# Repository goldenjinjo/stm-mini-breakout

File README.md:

# stm-mini-breakout
Breakout board for STM32H723ZGT6 MCU. Powered and programmed via USB C (FS). WIP.

Demonstration board for high-powered STM32s. 

## Schematics

# MCU

# Communication and Power

# Filtering, HSE Clock and Mounting Holes

## PCB Layout

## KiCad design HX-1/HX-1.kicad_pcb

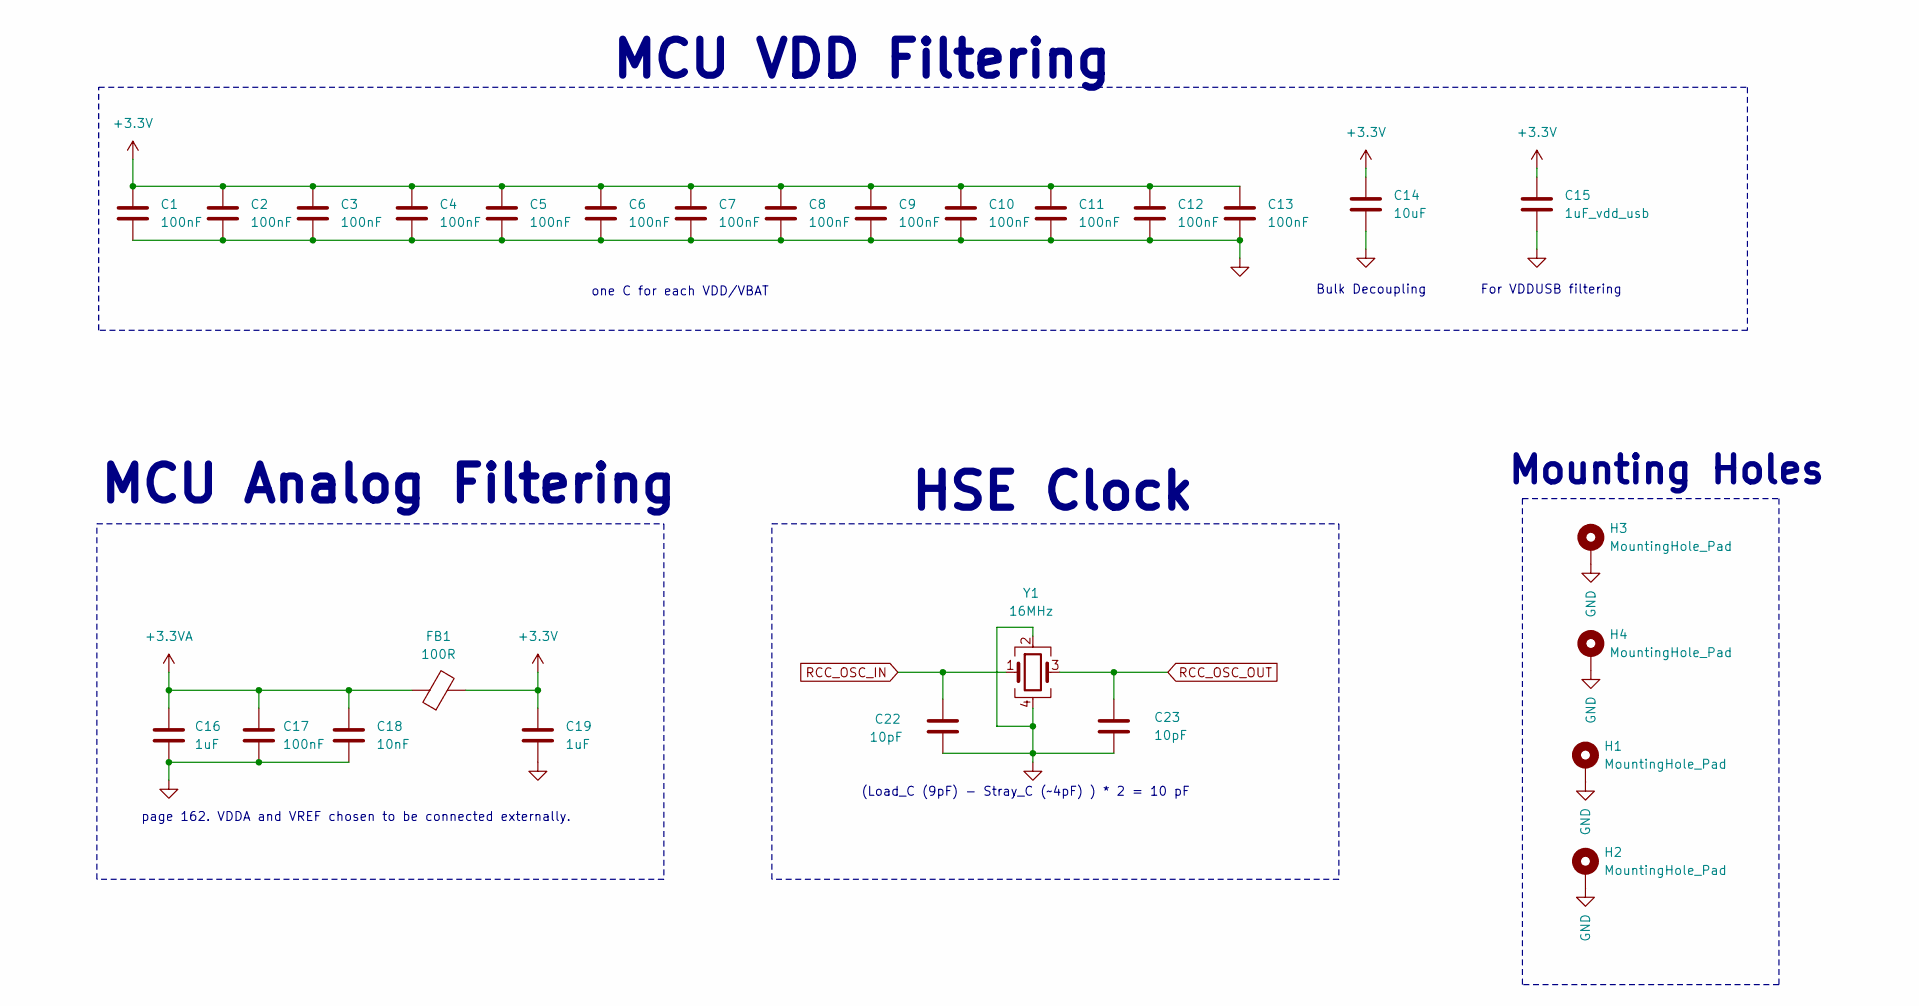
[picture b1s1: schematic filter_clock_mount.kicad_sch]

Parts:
C1, C2, C3, C4, C5, C6, C7, C8, C9, C10, C11, C12, C13, C17: 100nF; C_0402_1005Metric; LCSC PN C1525
C14: 10uF; C_0603_1608Metric; LCSC PN C19702
C15: 1uF_vdd_usb; C_0603_1608Metric; LCSC PN C15849
C16, C19: 1uF; C_0402_1005Metric; LCSC PN C52923
C18: 10nF; C_0603_1608Metric; LCSC PN C173276
C22, C23: 10pF; C_0603_1608Metric; LCSC PN C1634
FB1: 100R; R_0805_2012Metric; LCSC PN C1015
H1, H2, H3, H4: MountingHole_Pad; MountingHole_3.2mm_M3_Pad
Y1: 16MHz; Crystal_SMD_3225-4Pin_3.2x2.5mm; LCSC PN C13738

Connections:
+3.3V: C1.1, C2.1, C3.1, C4.1, C5.1, C6.1, C7.1, C8.1, C9.1, C10.1, C11.1, C12.1, C13.1, C14.1, C15.1, C19.1, FB1.2; also elsewhere on the board
+3.3VA: C16.1, C17.1, C18.1, FB1.1; also elsewhere on the board
GND: C1.2, C2.2, C3.2, C4.2, C5.2, C6.2, C7.2, C8.2, C9.2, C10.2, C11.2, C12.2, C13.2, C14.2, C15.2, C16.2, C17.2, C18.2, C19.2, C22.1, C23.2, H1.1, H2.1, H3.1, H4.1, Y1.2, Y1.4; also elsewhere on the board
RCC_OSC_IN: C22.2, Y1.1; also elsewhere on the board
RCC_OSC_OUT: C23.1, Y1.3; also elsewhere on the board

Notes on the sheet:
Bulk Decoupling
MCU Analog Filtering
page 162. VDDA and VREF chosen to be connected externally.
(Load_C (9pF) - Stray_C (~4pF) ) * 2 = 10 pF
one C for each VDD/VBAT
For VDDUSB filtering
HSE Clock
MCU VDD Filtering
Mounting Holes

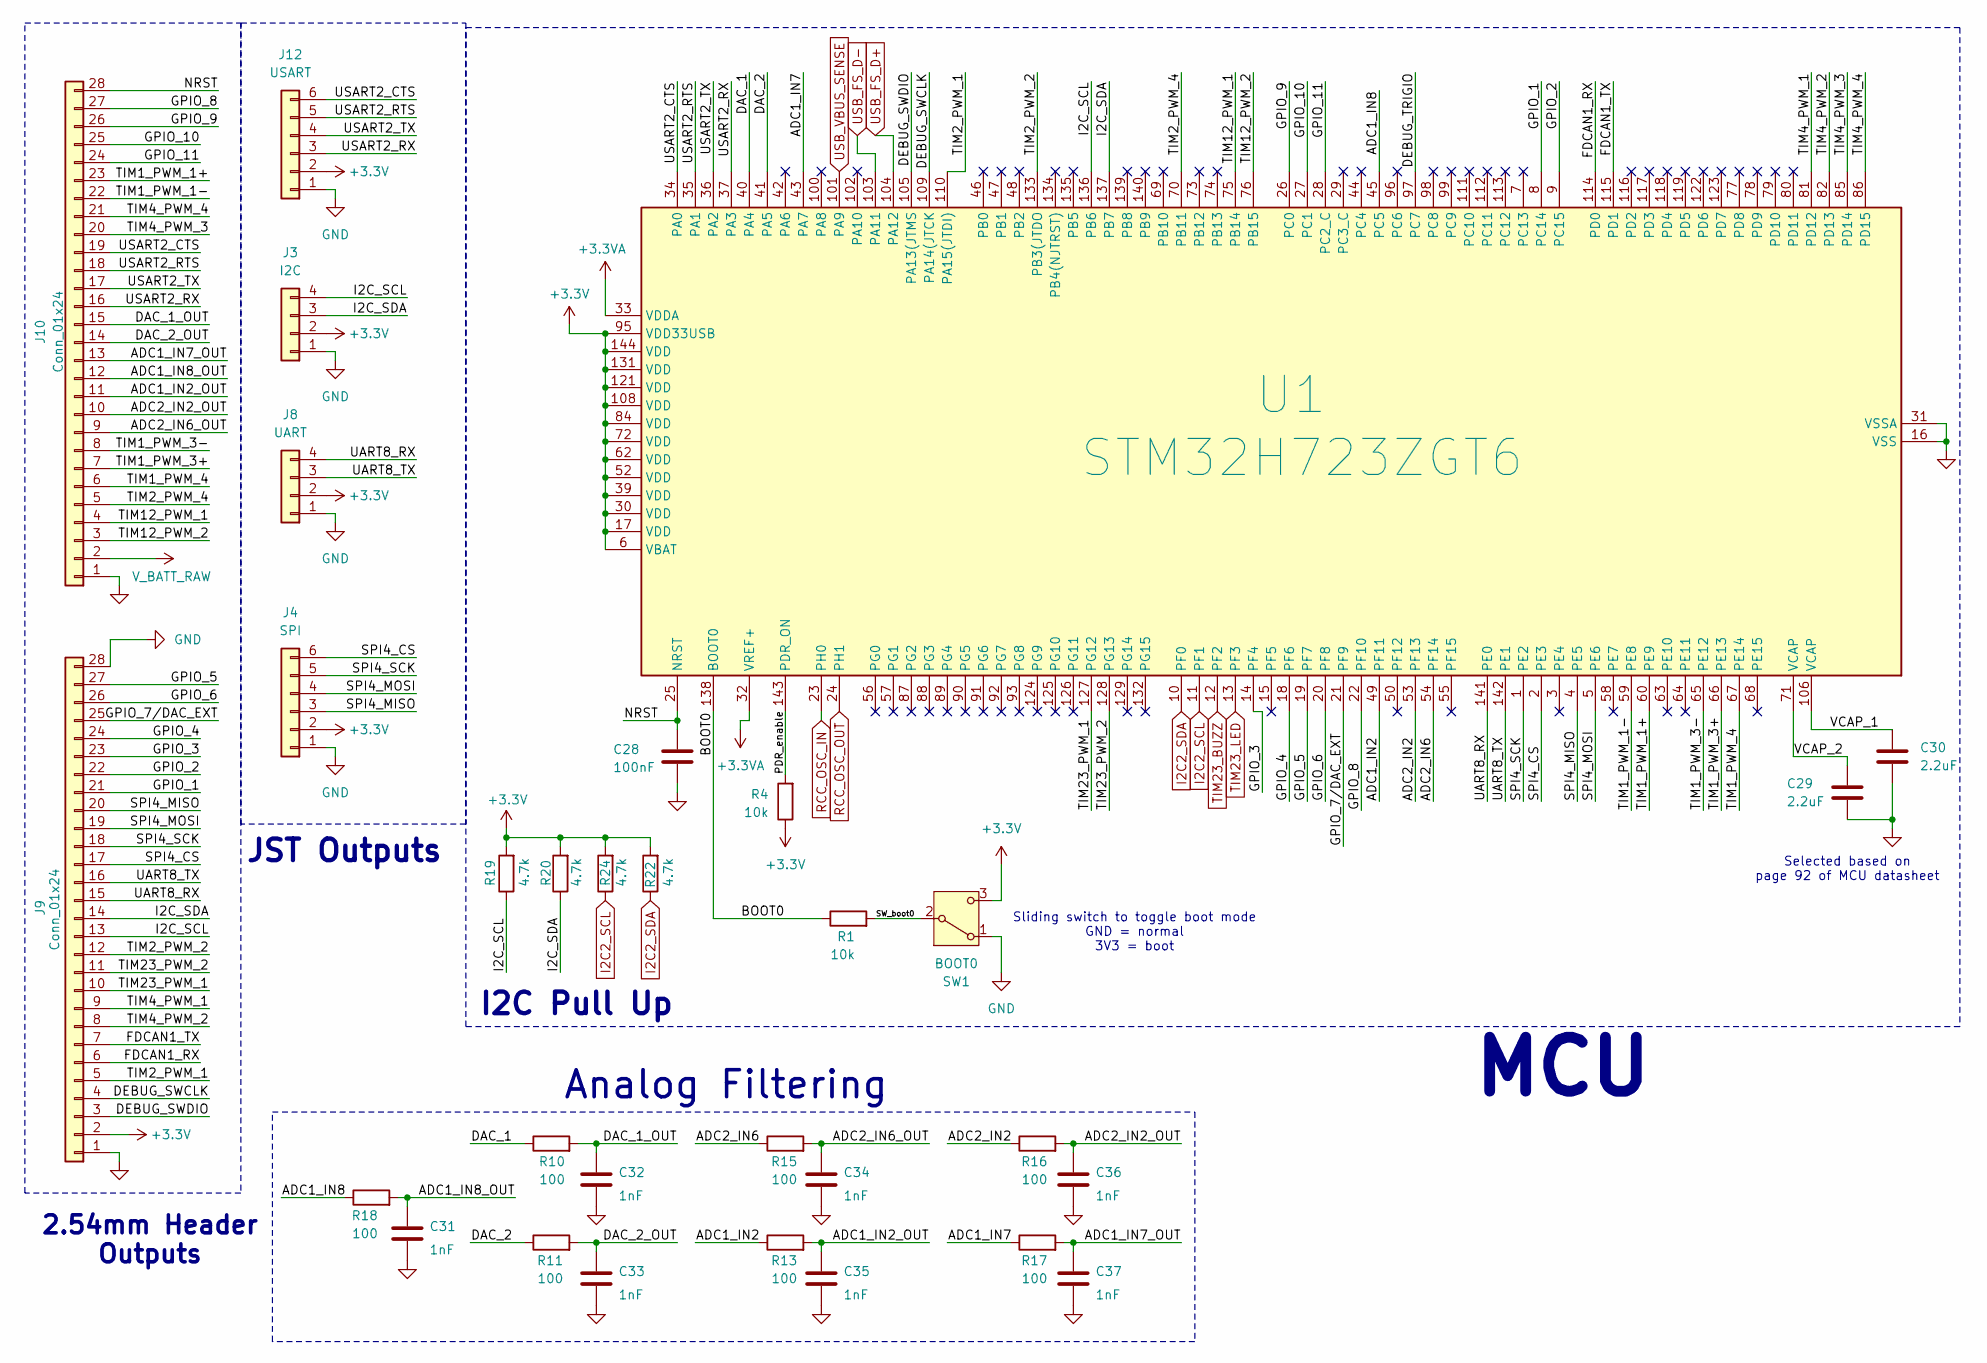
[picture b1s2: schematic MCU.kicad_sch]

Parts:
C28: 100nF; C_0402_1005Metric; LCSC PN C1525
C29, C30: 2.2uF; C_0603_1608Metric; LCSC PN C23630
C31, C32, C33, C34, C35, C36, C37: 1nF; C_0603_1608Metric; LCSC PN C1588
J3: I2C; JST_PH_B4B-PH-K_1x04_P2.00mm_Vertical; LCSC PN C131334
J4: SPI; JST_PH_B6B-PH-K_1x06_P2.00mm_Vertical; LCSC PN C131342
J8: UART; JST_PH_B4B-PH-K_1x04_P2.00mm_Vertical; LCSC PN C131334
J9, J10: Conn_01x24; PinHeader_1x28_P2.54mm_Vertical
J12: USART; JST_PH_B6B-PH-K_1x06_P2.00mm_Vertical; LCSC PN C131342
R1, R4: 10k; R_0402_1005Metric; LCSC PN C25744
R10, R11, R13, R15, R16, R17, R18: 100; R_0402_1005Metric; LCSC PN C25076
R19, R20, R22, R24: 4.7k; R_0402_1005Metric; LCSC PN C25900
SW1: BOOT0; SW-TH_G-SWITCH_SS-12F20-G070; LCSC PN C2848914
U1: STM32H723ZGT6; LQFP-144_20x20mm_P0.5mm; LCSC PN C730146

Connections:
+3.3V: J3.2, J4.2, J8.2, J9.2, J12.2, R4.1, R19.2, R20.2, R22.2, R24.2, SW1.3 (C), U1.6 (VBAT), U1.17 (VDD), U1.30 (VDD), U1.39 (VDD), U1.52 (VDD), U1.62 (VDD), U1.72 (VDD), U1.84 (VDD), U1.95 (VDD33USB), U1.108 (VDD), U1.121 (VDD), U1.131 (VDD), U1.144 (VDD); also elsewhere on the board
+3.3VA: U1.32 (VREF+), U1.33 (VDDA); also elsewhere on the board
/MCU/ADC1_IN2: R13.1, U1.49 (PF11)
/MCU/ADC1_IN2_OUT: C35.1, J10.11, R13.2
/MCU/ADC1_IN7: R17.1, U1.43 (PA7)
/MCU/ADC1_IN7_OUT: C37.1, J10.13, R17.2
/MCU/ADC1_IN8: R18.1, U1.45 (PC5)
/MCU/ADC1_IN8_OUT: C31.1, J10.12, R18.2
/MCU/ADC2_IN2: R16.1, U1.53 (PF13)
/MCU/ADC2_IN2_OUT: C36.1, J10.10, R16.2
/MCU/ADC2_IN6: R15.1, U1.54 (PF14)
/MCU/ADC2_IN6_OUT: C34.1, J10.9, R15.2
/MCU/BOOT0: R1.1, U1.138 (BOOT0)
/MCU/DAC_1: R10.1, U1.40 (PA4)
/MCU/DAC_1_OUT: C32.1, J10.15, R10.2
/MCU/DAC_2: R11.1, U1.41 (PA5)
/MCU/DAC_2_OUT: C33.1, J10.14, R11.2
/MCU/DEBUG_SWCLK: J9.4, U1.109 (PA14(JTCK)
/MCU/DEBUG_SWDIO: J9.3, U1.105 (PA13(JTMS)
/MCU/DEBUG_TRIGIO: U1.97 (PC7)
/MCU/FDCAN1_RX: J9.6, U1.114 (PD0)
/MCU/FDCAN1_TX: J9.7, U1.115 (PD1)
/MCU/GPIO_1: J9.21, U1.8 (PC14)
/MCU/GPIO_2: J9.22, U1.9 (PC15)
/MCU/GPIO_3: J9.23, U1.14 (PF4)
/MCU/GPIO_4: J9.24, U1.18 (PF6)
/MCU/GPIO_5: J9.27, U1.19 (PF7)
/MCU/GPIO_6: J9.26, U1.20 (PF8)
/MCU/GPIO_7/DAC_EXT: J9.25, U1.21 (PF9)
/MCU/GPIO_8: J10.27, U1.22 (PF10)
/MCU/GPIO_9: J10.26, U1.26 (PC0)
/MCU/GPIO_10: J10.25, U1.27 (PC1)
/MCU/GPIO_11: J10.24, U1.28 (PC2_C)
/MCU/I2C_SCL: J3.4, J9.13, R19.1, U1.136 (PB6)
/MCU/I2C_SDA: J3.3, J9.14, R20.1, U1.137 (PB7)
/MCU/NRST: C28.1, J10.28, U1.25 (NRST)
/MCU/PDR_enable: R4.2, U1.143 (PDR_ON)
/MCU/SPI4_CS: J4.6, J9.17, U1.2 (PE3)
/MCU/SPI4_MISO: J4.3, J9.20, U1.4 (PE5)
/MCU/SPI4_MOSI: J4.4, J9.19, U1.5 (PE6)
/MCU/SPI4_SCK: J4.5, J9.18, U1.1 (PE2)
/MCU/SW_boot0: R1.2, SW1.2 (B)
/MCU/TIM1_PWM_1+: J10.23, U1.60 (PE9)
/MCU/TIM1_PWM_1-: J10.22, U1.59 (PE8)
/MCU/TIM1_PWM_3+: J10.7, U1.66 (PE13)
/MCU/TIM1_PWM_3-: J10.8, U1.65 (PE12)
/MCU/TIM1_PWM_4: J10.6, U1.67 (PE14)
/MCU/TIM2_PWM_1: J9.5, U1.110 (PA15(JTDI))
/MCU/TIM2_PWM_2: J9.12, U1.133 (PB3(JTDO)
/MCU/TIM2_PWM_4: J10.5, U1.70 (PB11)
/MCU/TIM4_PWM_1: J9.9, U1.81 (PD12)
/MCU/TIM4_PWM_2: J9.8, U1.82 (PD13)
/MCU/TIM4_PWM_3: J10.20, U1.85 (PD14)
/MCU/TIM4_PWM_4: J10.21, U1.86 (PD15)
/MCU/TIM12_PWM_1: J10.4, U1.75 (PB14)
/MCU/TIM12_PWM_2: J10.3, U1.76 (PB15)
/MCU/TIM23_PWM_1: J9.10, U1.127 (PG12)
/MCU/TIM23_PWM_2: J9.11, U1.128 (PG13)
/MCU/UART8_RX: J8.4, J9.15, U1.141 (PE0)
/MCU/UART8_TX: J8.3, J9.16, U1.142 (PE1)
/MCU/USART2_CTS: J10.19, J12.6, U1.34 (PA0)
/MCU/USART2_RTS: J10.18, J12.5, U1.35 (PA1)
/MCU/USART2_RX: J10.16, J12.3, U1.37 (PA3)
/MCU/USART2_TX: J10.17, J12.4, U1.36 (PA2)
/MCU/VCAP_1: C30.1, U1.106 (VCAP)
/MCU/VCAP_2: C29.1, U1.71 (VCAP)
GND: C28.2, C29.2, C30.2, C31.2, C32.2, C33.2, C34.2, C35.2, C36.2, C37.2, J3.1, J4.1, J8.1, J9.1, J9.28, J10.1, J12.1, SW1.1 (A), U1.16 (VSS), U1.31 (VSSA), U1.38 (VSS), U1.51 (VSS), U1.61 (VSS), U1.83 (VSS), U1.94 (VSS), U1.107 (VSS), U1.120 (VSS), U1.130 (VSS); also elsewhere on the board
I2C2_SCL: R24.1, U1.11 (PF1); also elsewhere on the board
I2C2_SDA: R22.1, U1.10 (PF0); also elsewhere on the board
RCC_OSC_IN: U1.23 (PH0); also elsewhere on the board
RCC_OSC_OUT: U1.24 (PH1); also elsewhere on the board
TIM23_BUZZ: U1.12 (PF2); also elsewhere on the board
TIM23_LED: U1.13 (PF3); also elsewhere on the board
USB_FS_D+: U1.104 (PA12); also elsewhere on the board
USB_FS_D-: U1.103 (PA11); also elsewhere on the board
USB_VBUS_SENSE: U1.101 (PA9); also elsewhere on the board
V_BATT_RAW: J10.2; also elsewhere on the board

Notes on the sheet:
JST Outputs
2.54mm Header Outputs
MCU
Sliding switch to toggle boot mode GND = normal 3V3 = boot
I2C Pull Up
Analog Filtering
Selected based on page 92 of MCU datasheet

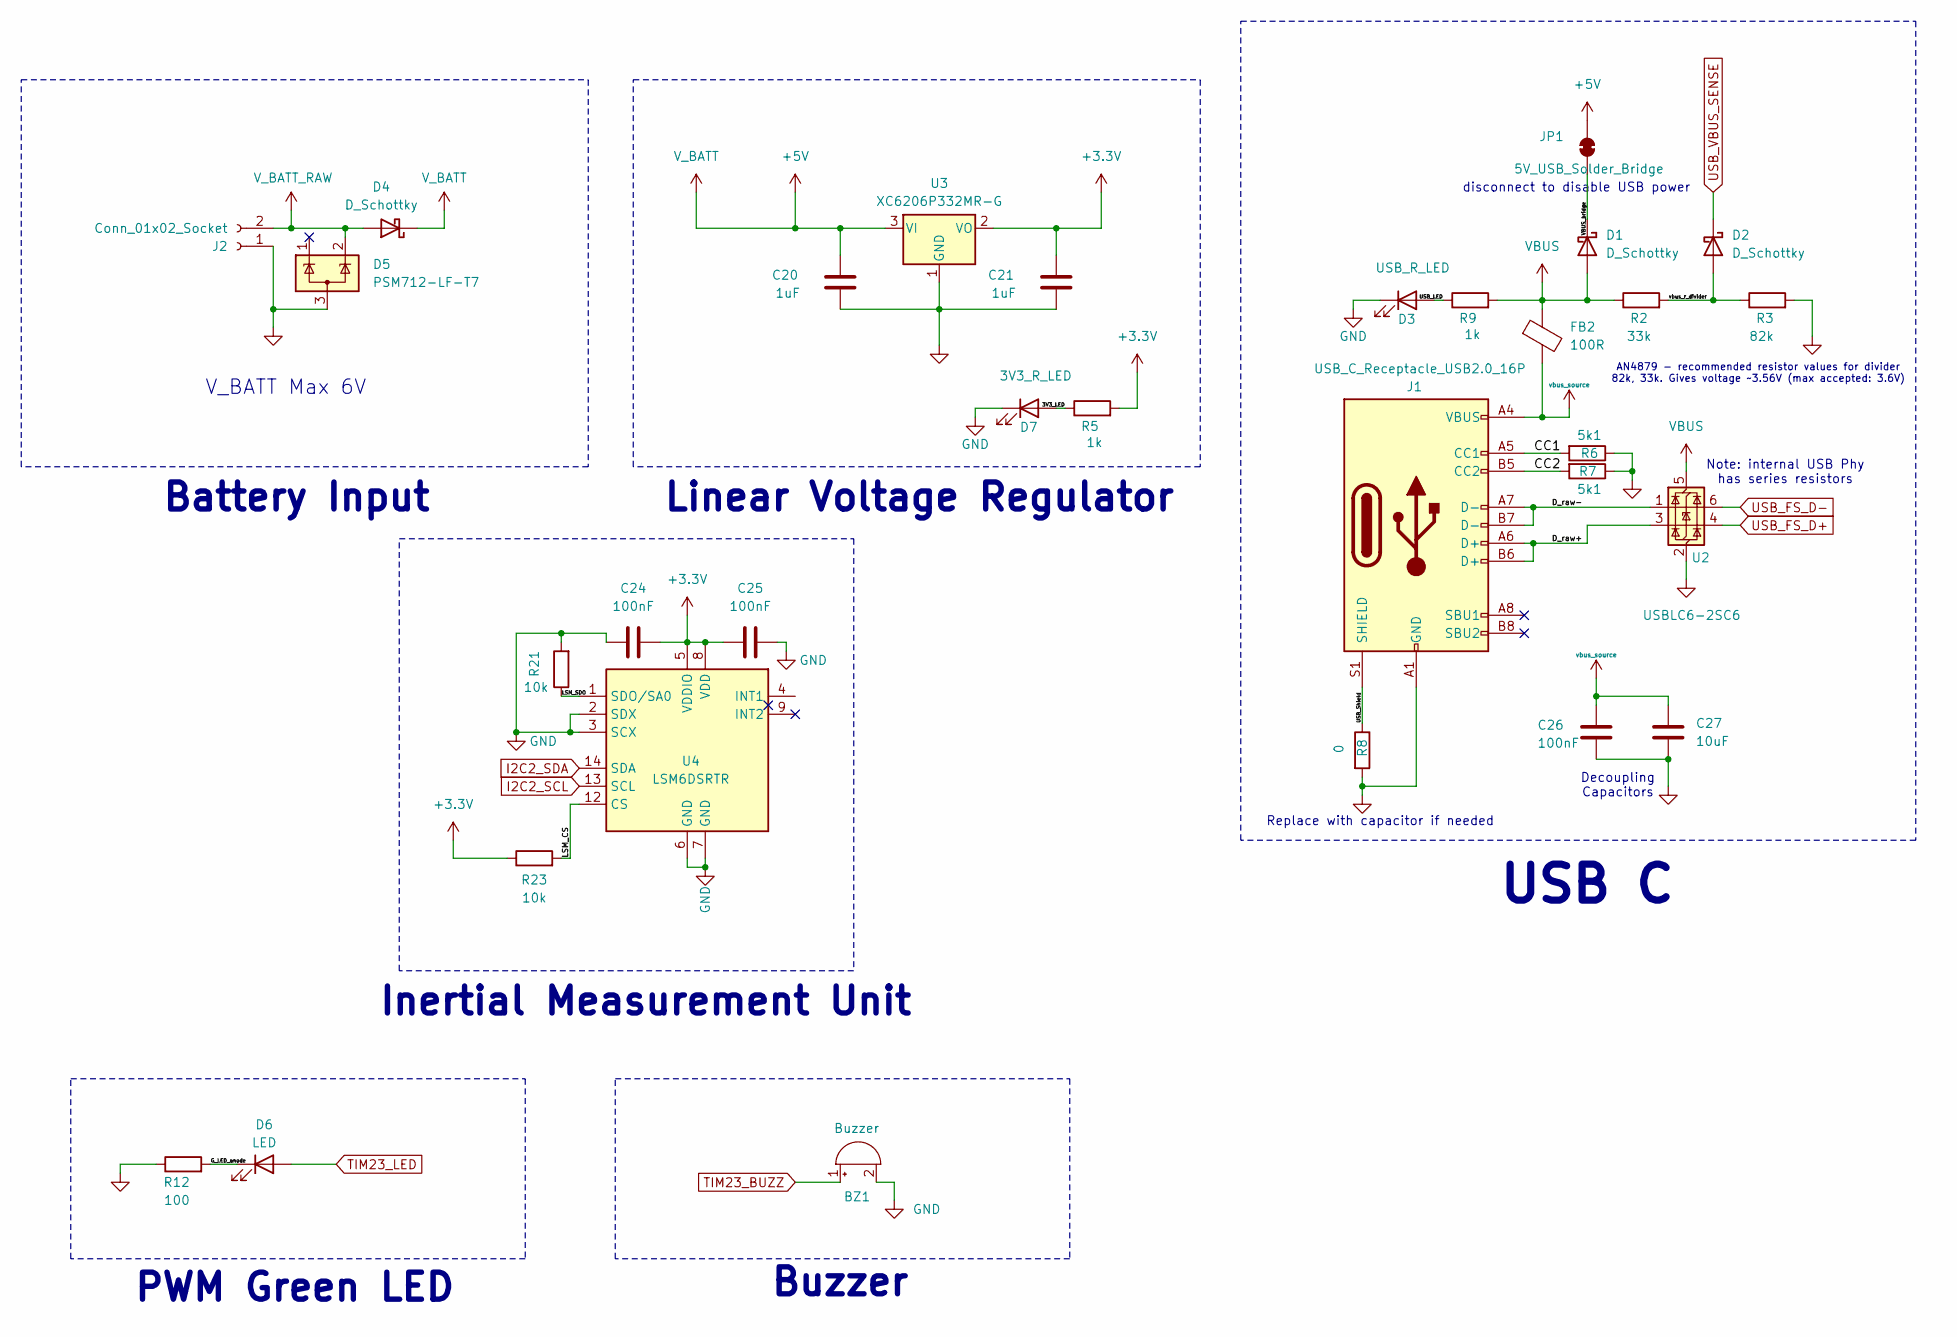
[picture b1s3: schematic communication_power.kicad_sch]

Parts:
BZ1: Buzzer; YUEXIN YX-SMD5020; LCSC PN C781883
C20, C21: 1uF; C_0402_1005Metric; LCSC PN C52923
C24, C25, C26: 100nF; C_0402_1005Metric; LCSC PN C1525
C27: 10uF; C_0603_1608Metric; LCSC PN C19702
D1, D2, D4: D_Schottky; D_SOD-323; LCSC PN C191023
D3: USB_R_LED; LED_0603_1608Metric; LCSC PN C2286
D5: PSM712-LF-T7; SOT-23-3; LCSC PN C32677
D6: LED; LED_0805_2012Metric; LCSC PN C2297
D7: 3V3_R_LED; LED_0603_1608Metric; LCSC PN C2286
FB2: 100R; R_0805_2012Metric; LCSC PN C1015
J1: USB_C_Receptacle_USB2.0_16P; USB_C_Receptacle_G-Switch_GT-USB-7010ASV; LCSC PN C2988369
J2: Conn_01x02_Socket; JST_PH_B2B-PH-K_1x02_P2.00mm_Vertical; LCSC PN C131337
JP1: 5V_USB_Solder_Bridge; SolderJumper-2_P1.3mm_Bridged_RoundedPad1.0x1.5mm
R2: 33k; R_0603_1608Metric; LCSC PN C4216
R3: 82k; R_0603_1608Metric; LCSC PN C23254
R5, R9: 1k; R_0603_1608Metric; LCSC PN C21190
R6, R7: 5k1; R_0603_1608Metric; LCSC PN C23186
R8: 0; R_0603_1608Metric; LCSC PN C21189
R12: 100; R_0402_1005Metric; LCSC PN C25076
R21, R23: 10k; R_0402_1005Metric; LCSC PN C25744
U2: USBLC6-2SC6; SOT-23-6; LCSC PN C7519
U3: XC6206P332MR-G; SOT-23-3; LCSC PN C5446
U4: LSM6DSRTR; LGA-14_3x2.5mm_P0.5mm_LayoutBorder3x4y; LCSC PN C784817

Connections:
+3.3V: C21.2, C24.2, C25.1, R5.2, R23.1, U3.2 (VO), U4.5 (VDDIO), U4.8 (VDD); also elsewhere on the board
+5V: C20.2, D4.1 (K), JP1.2 (B), U3.3 (VI)
/Communication and Power/3V3_LED: D7.2 (A), R5.1
/Communication and Power/CC1: J1.A5 (CC1), R6.2
/Communication and Power/CC2: J1.B5 (CC2), R7.2
/Communication and Power/D_raw+: J1.A6 (D+), J1.B6 (D+), U2.3 (I/O2)
/Communication and Power/D_raw-: J1.A7 (D-), J1.B7 (D-), U2.1 (I/O1)
/Communication and Power/G_LED_anode: D6.1 (K), R12.2
/Communication and Power/LSM_CS: R23.2, U4.12 (CS)
/Communication and Power/LSM_SDO: R21.1, U4.1 (SDO/SA0)
/Communication and Power/USB_LED: D3.2 (A), R9.1
/Communication and Power/USB_Shield: J1.S1 (SHIELD), R8.1
/Communication and Power/VBUS_bridge: D1.1 (K), JP1.1 (A)
/Communication and Power/vbus_r_divider: D2.2 (A), R2.2, R3.1
GND: BZ1.2 (+), C20.1, C21.1, C24.1, C25.2, C26.2, C27.2, D3.1 (K), D5.3 (A), D7.1 (K), J1.A1 (GND), J1.A12 (GND), J1.B1 (GND), J1.B12 (GND), J2.1, R3.2, R6.1, R7.1, R8.2, R12.1, R21.2, U2.2 (GND), U3.1 (GND), U4.2 (SDX), U4.3 (SCX), U4.6 (GND), U4.7 (GND); also elsewhere on the board
I2C2_SCL: U4.13 (SCL); also elsewhere on the board
I2C2_SDA: U4.14 (SDA); also elsewhere on the board
TIM23_BUZZ: BZ1.1 (-); also elsewhere on the board
TIM23_LED: D6.2 (A); also elsewhere on the board
USB_FS_D+: U2.4 (I/O2); also elsewhere on the board
USB_FS_D-: U2.6 (I/O1); also elsewhere on the board
USB_VBUS_SENSE: D2.1 (K); also elsewhere on the board
VBUS: D1.2 (A), FB2.1, R2.1, R9.2, U2.5 (VBUS)
V_BATT_RAW: D4.2 (A), D5.2 (K), J2.2; also elsewhere on the board
vbus_source: C26.1, C27.1, FB2.2, J1.A4 (VBUS), J1.A9 (VBUS), J1.B4 (VBUS), J1.B9 (VBUS)

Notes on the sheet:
PWM Green LED
Battery Input
V_BATT Max 6V
Linear Voltage Regulator
Replace with capacitor if needed
AN4879 - recommended resistor values for divider 82k, 33k. Gives voltage ~3.56V (max accepted: 3.6V)
Decoupling Capacitors
Buzzer
disconnect to disable USB power
Inertial Measurement Unit
Note: internal USB Phy has series resistors
USB C

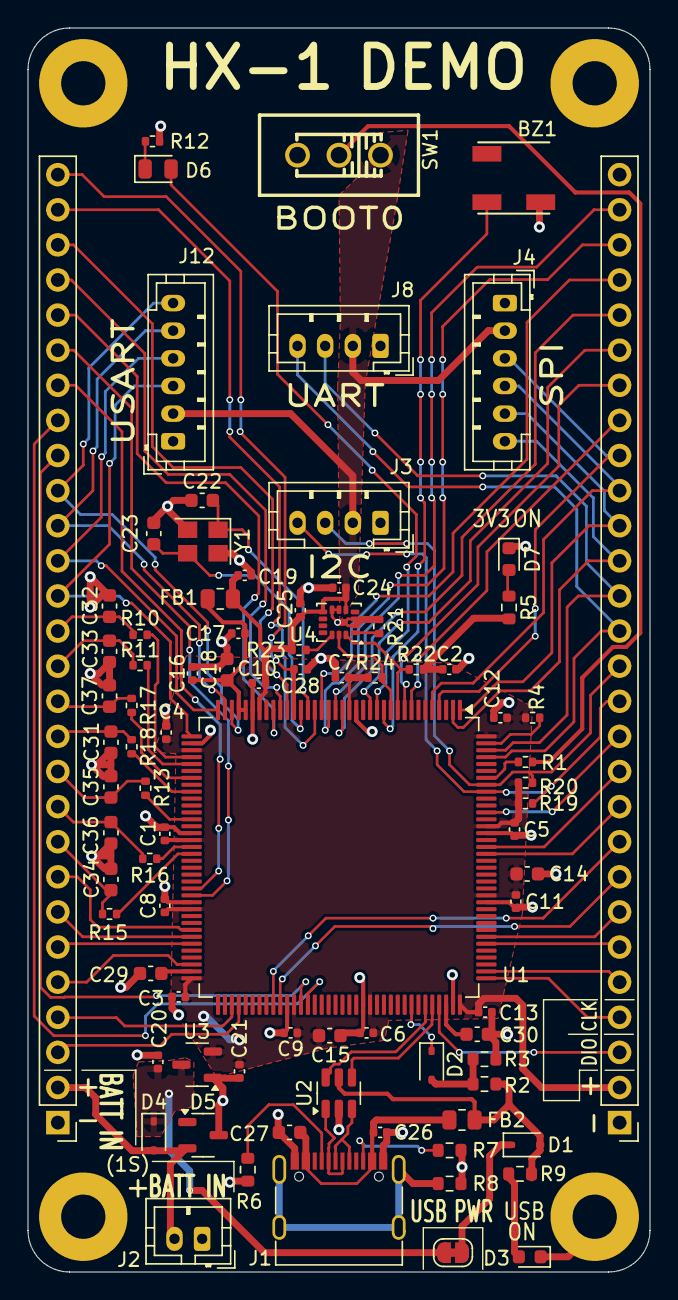
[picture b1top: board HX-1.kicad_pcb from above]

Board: 2 copper layers, 45.0 x 90.0 mm, 89 parts (0 on the bottom side), 91 nets.

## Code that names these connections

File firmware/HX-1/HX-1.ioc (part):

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Mcu.Name=STM32H723ZGTx
Mcu.Package=LQFP144
Mcu.UserName=STM32H723ZGTx
PA0.Mode=CTS_RTS
PA0.Signal=USART2_CTS
PA1.Mode=CTS_RTS
PA1.Signal=USART2_RTS
PA10.Signal=GPIO_Analog
PA11.Mode=Device_Only_FS
PA11.Signal=USB_OTG_HS_DM
PA12.Mode=Device_Only_FS
PA12.Signal=USB_OTG_HS_DP
PA13(JTMS/SWDIO).Mode=Serial_Wire
PA13(JTMS/SWDIO).Signal=DEBUG_JTMS-SWDIO
PA14(JTCK/SWCLK).Mode=Serial_Wire
PA14(JTCK/SWCLK).Signal=DEBUG_JTCK-SWCLK
PA15(JTDI).Signal=S_TIM2_CH1_ETR
PA2.Mode=Asynchronous
PA2.Signal=USART2_TX
PA3.Mode=Asynchronous
PA3.Signal=USART2_RX
PA4.Signal=COMP_DAC11_group
PA5.Signal=COMP_DAC12_group
PA6.Signal=GPIO_Analog
PA7.Signal=ADCx_INP7
PA8.Signal=GPIO_Analog
PA9.Mode=Activate_VBUS_FS
PA9.Signal=USB_OTG_HS_VBUS
PB0.Signal=GPIO_Analog
PB1.Signal=GPIO_Analog
PB10.Signal=GPIO_Analog
PB11.Signal=S_TIM2_CH4
PB13.Signal=GPIO_Analog
PB14.Signal=S_TIM12_CH1
PB15.Signal=S_TIM12_CH2
PB2.Signal=GPIO_Analog
PB3(JTDO/TRACESWO).Signal=S_TIM2_CH2
PB4(NJTRST).Signal=GPIO_Analog
PB5.Signal=GPIO_Analog
PB6.Mode=I2C
PB6.Signal=I2C1_SCL
PB7.Mode=I2C
PB7.Signal=I2C1_SDA
PB8.Signal=GPIO_Analog
PB9.Signal=GPIO_Analog
PC0.GPIOParameters=GPIO_Label
PC0.GPIO_Label=GPIO_9
PC0.Signal=GPIO_Output
PC1.GPIOParameters=GPIO_Label
PC1.GPIO_Label=GPIO_10
PC1.Signal=GPIO_Output
PC10.Signal=GPIO_Analog
PC11.Signal=GPIO_Analog
PC12.Signal=GPIO_Analog
PC13.Signal=GPIO_Analog
PC14-OSC32_IN.GPIOParameters=GPIO_Label
PC14-OSC32_IN.GPIO_Label=GPIO_1
PC14-OSC32_IN.Signal=GPIO_Output
PC15-OSC32_OUT.GPIOParameters=GPIO_Label
PC15-OSC32_OUT.GPIO_Label=GPIO_2
PC15-OSC32_OUT.Signal=GPIO_Output
PC2_C.GPIOParameters=GPIO_Label
PC2_C.GPIO_Label=GPIO_11
PC2_C.Signal=GPIO_Output
PC3_C.Signal=GPIO_Analog
PC4.Signal=GPIO_Analog
PC5.Signal=ADCx_INP8
PC6.Signal=GPIO_Analog
PC7.Mode=External_Trigger_bidirectional
PC7.Signal=DEBUG_TRGIO
PC8.Signal=GPIO_Analog
PC9.Signal=GPIO_Analog
PD0.Mode=FDCAN_Activate
PD0.Signal=FDCAN1_RX
PD1.Mode=FDCAN_Activate
PD1.Signal=FDCAN1_TX
PD10.Signal=GPIO_Analog
PD11.Signal=GPIO_Analog
PD12.Signal=S_TIM4_CH1
PD13.Signal=S_TIM4_CH2
PD14.Signal=S_TIM4_CH3
PD15.Signal=S_TIM4_CH4
PD2.Signal=GPIO_Analog
PD3.Signal=GPIO_Analog
PD4.Signal=GPIO_Analog
PD5.Signal=GPIO_Analog
PD6.Signal=GPIO_Analog
PD7.Signal=GPIO_Analog
PD8.Signal=GPIO_Analog
PD9.Signal=GPIO_Analog
PE0.Mode=Asynchronous
PE0.Signal=UART8_RX
PE1.Mode=Asynchronous
PE1.Signal=UART8_TX
PE10.Signal=GPIO_Analog
PE11.Signal=GPIO_Analog
PE12.Mode=PWM Generation3 CH3 CH3N
PE12.Signal=TIM1_CH3N
PE13.Signal=S_TIM1_CH3
PE14.Signal=S_TIM1_CH4
PE15.Signal=GPIO_Analog
PE2.Mode=Full_Duplex_Master
PE2.Signal=SPI4_SCK
PE3.GPIOParameters=GPIO_Label
PE3.GPIO_Label=SPI4_CS
PE3.Signal=GPIO_Output
PE4.Signal=GPIO_Analog
PE5.Mode=Full_Duplex_Master
PE5.Signal=SPI4_MISO
PE6.Mode=Full_Duplex_Master
PE6.Signal=SPI4_MOSI
PE7.Signal=GPIO_Analog
PE8.Mode=PWM Generation1 CH1 CH1N
PE8.Signal=TIM1_CH1N
PE9.Signal=S_TIM1_CH1
PF0.Mode=I2C
PF0.Signal=I2C2_SDA
PF1.Mode=I2C
PF1.Signal=I2C2_SCL
PF10.GPIOParameters=GPIO_Label
PF10.GPIO_Label=GPIO_8
PF10.Signal=GPIO_Output
PF11.Mode=IN2-Single-Ended
PF11.Signal=ADC1_INP2
PF12.Signal=GPIO_Analog
PF13.Mode=IN2-Single-Ended
PF13.Signal=ADC2_INP2
PF14.Mode=IN6-Single-Ended
PF14.Signal=ADC2_INP6
PF15.Signal=GPIO_Analog
PF2.GPIOParameters=GPIO_Label
PF2.GPIO_Label=TIM23_BUZZ
PF2.Signal=S_TIM23_CH3
PF3.GPIOParameters=GPIO_Label
PF3.GPIO_Label=TIM23_LED
PF3.Signal=S_TIM23_CH4
PF4.GPIOParameters=GPIO_Label
PF4.GPIO_Label=GPIO_3
PF4.Signal=GPIO_Output
PF5.Signal=GPIO_Analog
PF6.GPIOParameters=GPIO_Label
PF6.GPIO_Label=GPIO_4
PF6.Signal=GPIO_Output
PF7.GPIOParameters=GPIO_Label
PF7.GPIO_Label=GPIO_5
PF7.Signal=GPIO_Output
PF8.GPIOParameters=GPIO_Label
PF8.GPIO_Label=GPIO_6
PF8.Signal=GPIO_Output
PF9.GPIOParameters=GPIO_Label
PF9.GPIO_Label=GPIO_7/DAC_EXT
PF9.Signal=GPIO_Output
PF9.Stacked=true
PG0.Signal=GPIO_Analog
PG1.Signal=GPIO_Analog
PG10.Signal=GPIO_Analog
PG11.Signal=GPIO_Analog
PG12.Mode=PWM Generation1 CH1
PG12.Signal=TIM23_CH1
PG13.Signal=S_TIM23_CH2
PG14.Signal=GPIO_Analog
PG15.Signal=GPIO_Analog
PG2.Signal=GPIO_Analog
PG3.Signal=GPIO_Analog
PG4.Signal=GPIO_Analog
PG5.Signal=GPIO_Analog
PG6.Signal=GPIO_Analog
PG7.Signal=GPIO_Analog
PG8.Signal=GPIO_Analog
PG9.Signal=GPIO_Analog
PH0-OSC_IN.Mode=HSE-External-Oscillator
PH0-OSC_IN.Signal=RCC_OSC_IN
PH1-OSC_OUT.Mode=HSE-External-Oscillator
PH1-OSC_OUT.Signal=RCC_OSC_OUT
RCC.SYSCLKFreq_VALUE=64000000
board=custom

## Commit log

2025-04-14 initial mcu selection and placement
2025-04-15 add more power circuitry
2025-04-15 add footprints and lcsc pn for all passive components so far
2025-04-16 add some vbus circuitry and pin mappings for communication systems on mcu
2025-04-16 add script to automatically save schematic.svg, update readme to reference schematic.svg
2025-04-22 add firmware, update ioc file and schematic to have values for all mcu pins
2025-04-22 change schematic image to upload straight into docs folder, fix not auto updating
2025-04-22 update README with specific board used
2025-04-28 add crystal circuitry and dedicated sheets for comms and power
2025-04-28 move components to correct sheets, change net labels to global
2025-04-28 Update README with additional schematics
2025-04-28 add first draft of USB C design
2025-04-29 add LED and remaining footprints/LCSC PN to USB C circuit
2025-04-29 add vbus filtering and voltage regululator for 3.3V
2025-04-29 change almost all components to be basic jlcpcb parts
2025-04-29 add battery input circuit
2025-04-30 add mcu schematic file, change main to just link to other schematics. Update readme to show MCU schematic
2025-04-30 add buzzer, remove one ADC diff pair
2025-04-30 update firmware with removed analog signal
2025-04-30 remove uart7, spi2 and extra CS. Not needed. Start mapping GPIO
2025-04-30 add jst connectors to comms, add imu, start structuring pcb
2025-04-30 change most passive components to 0402 to save space
2025-04-30 draft board size
2025-04-30 change analog resistors to 0402 to make routing easier
2025-05-01 update scripts to export pcb svg
2025-05-01 increase size of layout image on readme
2025-05-01 add switch footprint
2025-05-02 change schottky diode to basic part from jlcpcb
2025-05-02 add 3v3 led and pwm led, position mounting holes and pin header
2025-05-03 map out traces for all I/Os, remove some ADC, PWM and GPIO for space
2025-05-03 change GPIO locations to optimise for output headers
2025-05-03 clean up schematic, layout more of pcb, fix some footprints
2025-05-16 add 3D model to usb
2025-05-16 remove fdcan connector for space, add header debug pin
2025-05-16 increase board height to 90mm to give more space to jst connectors
2025-05-16 renumber capacitors, position all MCU caps
2025-05-16 expand board width to 45mm to give space for component legends
2025-05-17 Position most of the passive components on pcb
2025-05-17 change USB capacitors to be fueled from VBUS_raw
2025-05-17 complete initial placement of all components, trace 5V
2025-05-17 remove 8 pin header on top of board, extend side headers by 4 each to replace pins
2025-05-17 remove GPIO 12 and DEBUG conn, add debug to right header
2025-05-17 add silkscreen for batt in
2025-05-17 remove 3V3 out and replace with standard 3V3 in.
2025-05-17 remove GPIO 12 from MCU and firmware
2025-05-17 remove forgotten excess GPIO pins
2025-06-12 remove schematic design for dedicated 3V3 out
2025-06-12 remove deprecated debug header, improve silkscreen pin designators
2025-06-12 route power traces
2025-06-12 create ground plane and route ground traces
2025-06-12 route missing 3v3 traces
2025-06-13 add 3v3 pour under MCU, complete routing of 3v3 traces
2025-06-13 route usb trace and fix 3v3 pours
2025-06-13 increase edge spacing to 4mm for mounting holes
2025-06-16 remove copper plot from svg to fix gnd plane blocking everything. route some signal traces
2025-06-16 draft traces of left side of MCU
2025-06-17 route USART traces, flip pin 18 and pin 19 on left header
2025-06-17 route more of left side, change copper clearances based on jlcpcb
2025-06-17 fix hole clearances, write custom rule for USB C to stop mechanical hole clearance error
2025-06-17 remove silkscreen too close to pad on buzzer, adjust via for gnd plane
2025-06-17 complete route of left side of board, flip cts and rts pins on jst connector
2025-06-17 rearrange some analog voltage components, connect missing 3v3 traces
2025-06-17 trace some of the right side pins
2025-06-17 replace right header pin for BOOT with GND, remove PIN control of BOOT for simplicity
2025-06-19 adjust left side traces and components for better ground plane
2025-06-23 change pin ordering of SPI on left header for better routing, route some of the left traces
2025-06-23 connect remaining traces
2025-06-23 remove unuused pull up resistor on D+ USB, too difficult to trace and unneccesary
2025-06-23 flip TWM_PWM+1 and -1 for better routing, improve routing for better gnd planes
2025-06-23 clean up left side traces, flip TWM1_PWM1 traces back as vias had them flipped
2025-06-23 generally improve gnd plane, reduce min gnd plane width to 0.2mm
2025-06-23 further refine copper pours and traces, clean up Fab layer
2025-06-23 add name, date and jlc tag
2025-07-05 tidy up schematics and change groupings on each sheet
2025-07-05 change schematic file name and doc, script references
2025-07-05 update README with new sch names
2025-07-05 change readme title blocks for new sch names
2025-07-05 add bold text to filtering sch sheet :
2025-12-24 improve silkscreen legibility, add manufacturing files
2025-12-24 add an extra JLC to order number mark
2025-12-24 add assembly files, fix reference designators
2025-12-24 change LSM6DS to version compat with jlcpcb economic pcba
